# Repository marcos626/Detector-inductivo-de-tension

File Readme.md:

# Detector inductivo de tensión

Diseño en PCB con Kicad de un detector de tensión alterna.

## Esquemático

## Vista 3D PCB

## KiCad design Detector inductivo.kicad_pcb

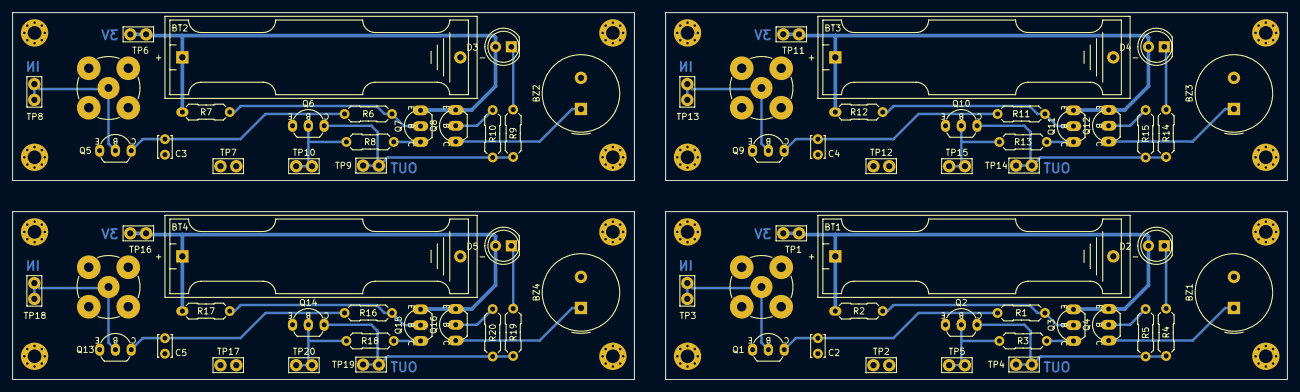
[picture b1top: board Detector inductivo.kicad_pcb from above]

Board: 2 copper layers, 205.0 x 59.0 mm, 92 parts (0 on the bottom side), 11 nets.

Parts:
AE2, AE3, AE4, AE5: Antenna_Shield; BNC_TEConnectivity_1478204_Vertical
BT1, BT2, BT3, BT4: 3V; BatteryHolder_Keystone_2466_1xAAA
BZ1, BZ2, BZ3, BZ4: Buzzer; Buzzer_TDK_PS1240P02BT_D12.2mm_H6.5mm
C2, C3, C4, C5: 100nF; C_Disc_D3.4mm_W2.1mm_P2.50mm
D2, D3, D4, D5: LED_Filled; LED_D5.0mm
H1, H1#2, H1#3, H1#4, H2, H3, H4, H5, H6, H7, H8, H9, H10, H11, H12, H13: MountingHole; MountingHole_2.2mm_M2_Pad_Via
Q1, Q2, Q5, Q6, Q9, Q10, Q13, Q14: 2N2222A-TO92; TO-92_Inline_Wide_EBC_2N-2222
Q3, Q4, Q7, Q8, Q11, Q12, Q15, Q16: BC557; TO-92_Inline_Wide_marcos
R1, R3, R6, R8, R11, R13, R16, R18: 100k; R_Axial_DIN0207_L6.3mm_D2.5mm_P7.62mm_Horizontal
R2, R7, R12, R17: 1M; R_Axial_DIN0207_L6.3mm_D2.5mm_P7.62mm_Horizontal
R4, R9, R14, R19: 47; R_Axial_DIN0207_L6.3mm_D2.5mm_P7.62mm_Horizontal
R5, R10, R15, R20: 10k; R_Axial_DIN0207_L6.3mm_D2.5mm_P7.62mm_Horizontal
TP1, TP2, TP3, TP4, TP5, TP6, TP7, TP8, TP9, TP10, TP11, TP12, TP13, TP14, TP15, TP16, TP17, TP18, TP19, TP20: TestPoint_Probe; TestPoint_Bridge_Pitch2.54mm_Drill1.0mm

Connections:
+3V: BT1.1 (+), BT2.1 (+), BT3.1 (+), BT4.1 (+), D2.2 (A), D3.2 (A), D4.2 (A), D5.2 (A), Q3.3 (E), Q4.3 (E), Q7.3 (E), Q8.3 (E), Q11.3 (E), Q12.3 (E), Q15.3 (E), Q16.3 (E), R2.1, R7.1, R12.1, R17.1, TP1.1, TP6.1, TP11.1, TP16.1
/INPUT: AE2.1 (A), AE3.1 (A), AE4.1 (A), AE5.1 (A), Q1.2 (B), Q5.2 (B), Q9.2 (B), Q13.2 (B), TP3.1, TP8.1, TP13.1, TP18.1
/OUTPUT: Q2.3 (C), Q6.3 (C), Q10.3 (C), Q14.3 (C), R4.2, R5.1, R9.2, R10.1, R14.2, R15.1, R19.2, R20.1, TP4.1, TP9.1, TP14.1, TP19.1
GND: AE2.2 (Shield), AE3.2 (Shield), AE4.2 (Shield), AE5.2 (Shield), BT1.2 (-), BT2.2 (-), BT3.2 (-), BT4.2 (-), BZ1.2 (-), BZ2.2 (-), BZ3.2 (-), BZ4.2 (-), C2.2, C3.2, C4.2, C5.2, Q1.1 (E), Q2.1 (E), Q5.1 (E), Q6.1 (E), Q9.1 (E), Q10.1 (E), Q13.1 (E), Q14.1 (E), TP2.1, TP7.1, TP12.1, TP17.1
unnamed: BZ1.1 (+), BZ2.1 (+), BZ3.1 (+), BZ4.1 (+), Q4.1 (C), Q8.1 (C), Q12.1 (C), Q16.1 (C)
unnamed: D2.1 (K), D3.1 (K), D4.1 (K), D5.1 (K), R4.1, R9.1, R14.1, R19.1
unnamed: C2.1, C3.1, C4.1, C5.1, Q1.3 (C), Q5.3 (C), Q9.3 (C), Q13.3 (C), R1.1, R6.1, R11.1, R16.1
unnamed: Q2.2 (B), Q6.2 (B), Q10.2 (B), Q14.2 (B), R3.2, R8.2, R13.2, R18.2, TP5.1, TP10.1, TP15.1, TP20.1
unnamed: Q3.2 (B), Q7.2 (B), Q11.2 (B), Q15.2 (B), R1.2, R2.2, R6.2, R7.2, R11.2, R12.2, R16.2, R17.2
unnamed: Q3.1 (C), Q7.1 (C), Q11.1 (C), Q15.1 (C), R3.1, R8.1, R13.1, R18.1
unnamed: Q4.2 (B), Q8.2 (B), Q12.2 (B), Q16.2 (B), R5.2, R10.2, R15.2, R20.2

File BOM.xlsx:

Reference | Qty | Value | Footprint
AE2 | 1 | Antenna_Shield | Connector_Coaxial:BNC_TEConnectivity_1478204_Vertical
BT1 | 1 | 3V | Connector_Wire:SolderWire-0.1sqmm_1x02_P3.6mm_D0.4mm_OD1mm
BZ1 | 1 | Buzzer | Buzzer_Beeper:Buzzer_TDK_PS1240P02BT_D12.2mm_H6.5mm
C2 | 1 | 100nF | Capacitor_THT:C_Disc_D3.4mm_W2.1mm_P2.50mm
D2 | 1 | LED_Filled | LED_THT:LED_D5.0mm
Q1,Q2 | 2 | 2N2222A-TO92 | PCM_Package_TO_SOT_THT_AKL:TO-92_Inline_Wide_EBC
Q3,Q4 | 2 | BC557 | Library:TO-92_Inline_Wide_marcos
R1,R3 | 2 | 100k | PCM_Resistor_THT_AKL:R_Axial_DIN0207_L6.3mm_D2.5mm_P7.62mm_Horizontal
R2 | 1 | 1M | PCM_Resistor_THT_AKL:R_Axial_DIN0207_L6.3mm_D2.5mm_P7.62mm_Horizontal
R4 | 1 | 47 | PCM_Resistor_THT_AKL:R_Axial_DIN0207_L6.3mm_D2.5mm_P7.62mm_Horizontal
R5 | 1 | 10k | PCM_Resistor_THT_AKL:R_Axial_DIN0207_L6.3mm_D2.5mm_P7.62mm_Horizontal
TP1,TP2,TP3,TP4,TP5 | 5 | TestPoint_Probe | TestPoint:TestPoint_Bridge_Pitch2.0mm_Drill0.7mm

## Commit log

2025-05-10 add files
2025-05-10 Add Readme
